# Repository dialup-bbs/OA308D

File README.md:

# OA308D
All Discrete LM308 Op-Amp - The rare, classic and out of print LM308 Op-Amp using all discrete components.

Based on detailed schematic as presented in the Linear Technology datasheet. Transistor component reference numbers are the same.

This is an untested work in progress. Please do not build if you do not know what you are doing. Three prototype boards are currently under fabrication. Any corrections, feedback, comments or recommendations are highly encouraged.

This is also my second KiCad project and as a builder, I am completely unexperienced as a circuit drafter/designer.

This project is totally influenced by MostlyDIYrf/K7TFC's OA741D.

https://github.com/mostlydiyrf/OA741D

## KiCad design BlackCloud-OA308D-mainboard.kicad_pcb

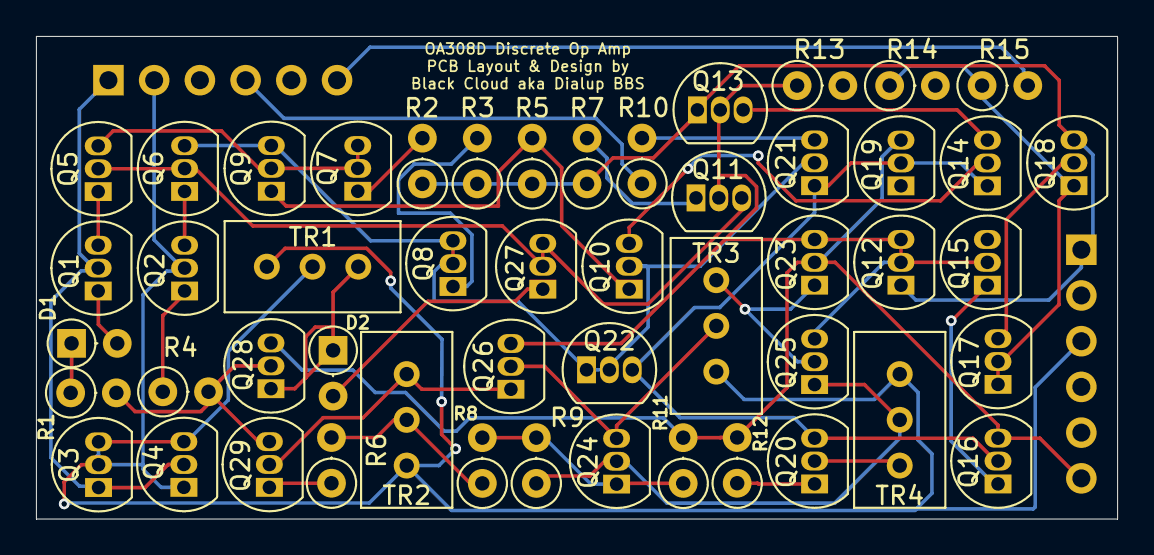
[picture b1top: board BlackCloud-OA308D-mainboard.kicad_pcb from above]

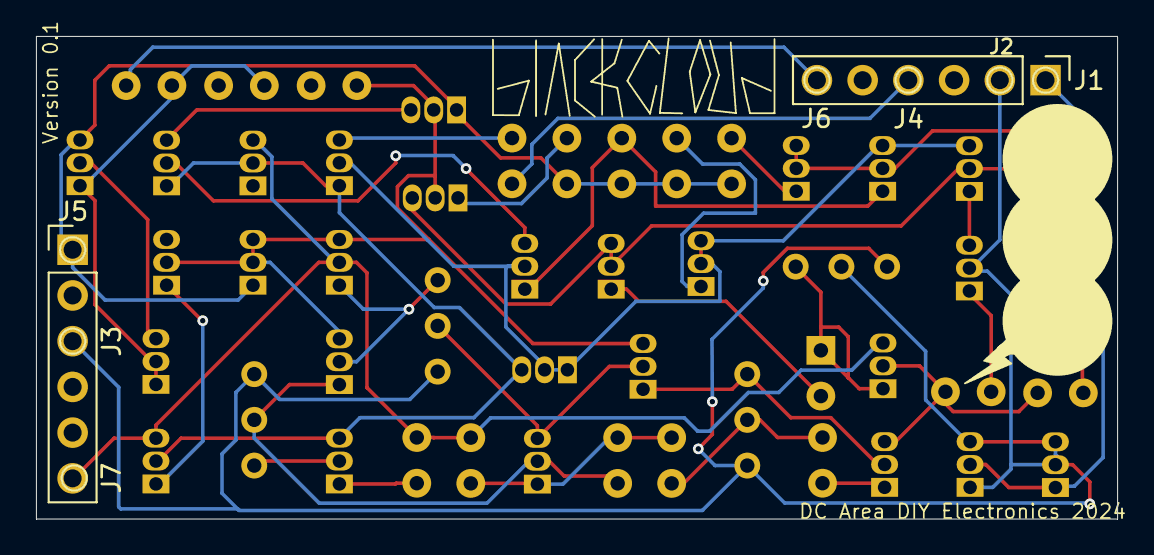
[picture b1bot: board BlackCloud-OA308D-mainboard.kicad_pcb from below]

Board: 2 copper layers, 60.1 x 26.8 mm, 57 parts (7 on the bottom side), 40 nets.

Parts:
D1, D2: 1N5711; D_DO-35_SOD27_P2.54mm_Vertical_AnodeUp
J1, J2, J5, J6, J7: Conn_01x01; TestPoint_Pad_D1.0mm
J3: Compensation 1; TestPoint_Pad_D1.0mm
J4: Compensation 8; TestPoint_Pad_D1.0mm
Q1, Q2, Q3, Q4, Q5, Q6, Q14, Q15, Q17, Q18, Q20, Q21, Q24, Q25, Q26, Q27, Q29: 2N3904; TO-92_Inline
Q7, Q8, Q9, Q10, Q11, Q12, Q16, Q19, Q28: 2N3906; TO-92_Inline
Q13: NPN; TO-92_Inline
Q22: TO-92_Inline
Q23: NJFET; TO-92_Inline
R1, R4, R13: 2k; R_Axial_DIN0207_L6.3mm_D2.5mm_P2.54mm_Vertical
R2, R3, R9: 20k; R_Axial_DIN0207_L6.3mm_D2.5mm_P2.54mm_Vertical
R5, R7: 10k; R_Axial_DIN0207_L6.3mm_D2.5mm_P2.54mm_Vertical
R6: 6.4k; R_Axial_DIN0207_L6.3mm_D2.5mm_P2.54mm_Vertical
R8: 500ohm; R_Axial_DIN0207_L6.3mm_D2.5mm_P2.54mm_Vertical
R10: 5.6k; R_Axial_DIN0207_L6.3mm_D2.5mm_P2.54mm_Vertical
R11: 1k; R_Axial_DIN0207_L6.3mm_D2.5mm_P2.54mm_Vertical
R12: 820ohm; R_Axial_DIN0207_L6.3mm_D2.5mm_P2.54mm_Vertical
R14: 240ohm; R_Axial_DIN0207_L6.3mm_D2.5mm_P2.54mm_Vertical
R15: 90ohm; R_Axial_DIN0207_L6.3mm_D2.5mm_P2.54mm_Vertical
TR1: 50k; Potentiometer_Bourns_3386C_Horizontal
TR2: 60k; Potentiometer_Bourns_3386C_Horizontal
TR3: 940ohm; Potentiometer_Bourns_3386C_Horizontal
TR4: 20k; Potentiometer_Bourns_3386C_Horizontal

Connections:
unnamed: D1.2 (A), Q1.1 (E)
unnamed: D1.1 (K), R1.1
unnamed: D2.2 (A), Q27.1 (E)
unnamed: D2.1 (K), Q28.1 (E), TR1.1
unnamed: J1.1, Q1.2 (B), Q3.1 (E), Q4.2 (B)
unnamed: J2.1, Q2.2 (B), Q4.1 (E)
unnamed: Q6.3 (C), Q8.2 (B), Q8.3 (C), Q9.3 (C), Q10.2 (B), Q21.2 (B), Q22.1 (C), Q22.2 (B)
unnamed: J4.1, R10.1
unnamed: J5.1, Q12.1 (E), Q13.1 (C), Q18.3 (C), R2.1, R3.1, R5.1, R7.1
unnamed: J6.1, R15.2
unnamed: J7.1, Q16.3 (C), Q19.3 (C), Q23.2 (G), Q28.3 (C), R11.2, R12.2
unnamed: Q1.3 (C), Q5.1 (E)
unnamed: Q2.3 (C), Q6.1 (E)
unnamed: Q2.1 (E), R4.1
unnamed: Q4.3 (C), TR1.2
unnamed: Q5.3 (C), Q7.2 (B), Q7.3 (C), Q9.2 (B)
unnamed: Q7.1 (E), R2.2
unnamed: Q8.1 (E), R3.2
unnamed: Q10.3 (C), Q14.2 (B)
unnamed: Q9.1 (E), Q10.1 (E), R5.2
unnamed: Q11.2 (B), Q12.2 (B), Q12.3 (C), Q13.2 (B), Q15.2 (B), Q23.3 (S), Q25.3 (C), Q26.3 (C), R13.1
unnamed: Q5.2 (B), Q6.2 (B), Q11.3 (C), Q27.2 (B), Q27.3 (C)
unnamed: Q11.1 (E), R7.2
unnamed: Q13.3 (E), Q14.3 (C)
unnamed: Q14.1 (E), Q16.2 (B), Q19.2 (B), Q20.3 (C), Q21.1 (E), Q22.3 (E)
unnamed: Q15.3 (C), Q17.3 (C), Q18.2 (B), R13.2
unnamed: Q15.1 (E), Q16.1 (E)
unnamed: Q17.1 (E), Q17.2 (B), Q18.1 (E), R14.1, R15.1
unnamed: Q19.1 (E), R14.2
unnamed: Q20.2 (B), TR4.1
unnamed: Q20.1 (E), R12.1
unnamed: Q21.3 (C), R10.2
unnamed: Q23.1 (D), Q25.2 (B), TR3.1
unnamed: Q24.2 (B), Q25.1 (E), R9.1, TR4.2
unnamed: Q24.3 (C), Q26.2 (B), TR3.2
unnamed: Q24.1 (E), R8.2, R9.2, R11.1
unnamed: Q26.1 (E), Q29.2 (B), TR2.1
unnamed: Q28.2 (B), Q29.3 (C), R1.2, R4.2
unnamed: Q29.1 (E), R6.1
unnamed: R6.2, R8.1, TR2.2

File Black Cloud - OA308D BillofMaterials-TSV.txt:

Reference	Value	Datasheet	Footprint	Qty	DNP
D1,D2	1N5711	https://www.microsemi.com/document-portal/doc_download/8865-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	Diode_THT:D_DO-35_SOD27_P7.62mm_Horizontal	2	
J1,J2,J5,J6,J7	Conn_01x01	~	Connector_PinHeader_2.54mm:PinHeader_1x01_P2.54mm_Vertical	5	
J3	Compensation 1	~	Connector_PinHeader_2.54mm:PinHeader_1x01_P2.54mm_Vertical	1	
J4	Compensation 8	~	Connector_PinHeader_2.54mm:PinHeader_1x01_P2.54mm_Vertical	1	
Q1,Q2,Q3,Q4,Q5,Q6,Q14,Q15,Q17,Q18,Q20,Q21,Q24,Q25,Q26,Q27,Q29	2N3904	https://www.onsemi.com/pub/Collateral/2N3903-D.PDF	Package_TO_SOT_THT:TO-92_Inline	17	
Q7,Q8,Q9,Q10,Q11,Q12,Q16,Q19,Q28	2N3906	https://www.onsemi.com/pub/Collateral/2N3906-D.PDF	Package_TO_SOT_THT:TO-92_Inline	9	
Q13	NPN	https://ngspice.sourceforge.io/docs/ngspice-html-manual/manu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	Package_TO_SOT_THT:TO-92_Inline	1	
Q22	~	https://ngspice.sourceforge.io/docs/ngspice-html-manual/manu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	Package_TO_SOT_THT:TO-92_Inline	1	
Q23	NJFET	https://ngspice.sourceforge.io/docs/ngspice-html-manual/manu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	Package_TO_SOT_THT:TO-92_Inline	1	
R1,R4,R13	2k	~	Resistor_THT:R_Axial_DIN0207_L6.3mm_D2.5mm_P2.54mm_Vertical	3	
R2,R3,R9,TR4	20k	~	-- mixed values --	4	
R5,R7	10k	~	Resistor_THT:R_Axial_DIN0207_L6.3mm_D2.5mm_P2.54mm_Vertical	2	
R6	6.4k	~	Resistor_THT:R_Axial_DIN0207_L6.3mm_D2.5mm_P2.54mm_Vertical	1	
R8	500ohm	~	Resistor_THT:R_Axial_DIN0207_L6.3mm_D2.5mm_P2.54mm_Vertical	1	
R10	5.6k	~	Resistor_THT:R_Axial_DIN0207_L6.3mm_D2.5mm_P2.54mm_Vertical	1	
R11	1k	~	Resistor_THT:R_Axial_DIN0207_L6.3mm_D2.5mm_P2.54mm_Vertical	1	
R12	820ohm	~	Resistor_THT:R_Axial_DIN0207_L6.3mm_D2.5mm_P2.54mm_Vertical	1	
R14	240ohm	~	Resistor_THT:R_Axial_DIN0207_L6.3mm_D2.5mm_P2.54mm_Vertical	1	
R15	90ohm	~	Resistor_THT:R_Axial_DIN0207_L6.3mm_D2.5mm_P2.54mm_Vertical	1	
TR1	50k	~	Potentiometer_THT:Potentiometer_Bourns_3386C_Horizontal	1	
TR2	60k	~	Potentiometer_THT:Potentiometer_Bourns_3386C_Horizontal	1	
TR3	940ohm	~	Potentiometer_THT:Potentiometer_Bourns_3386C_Horizontal	1

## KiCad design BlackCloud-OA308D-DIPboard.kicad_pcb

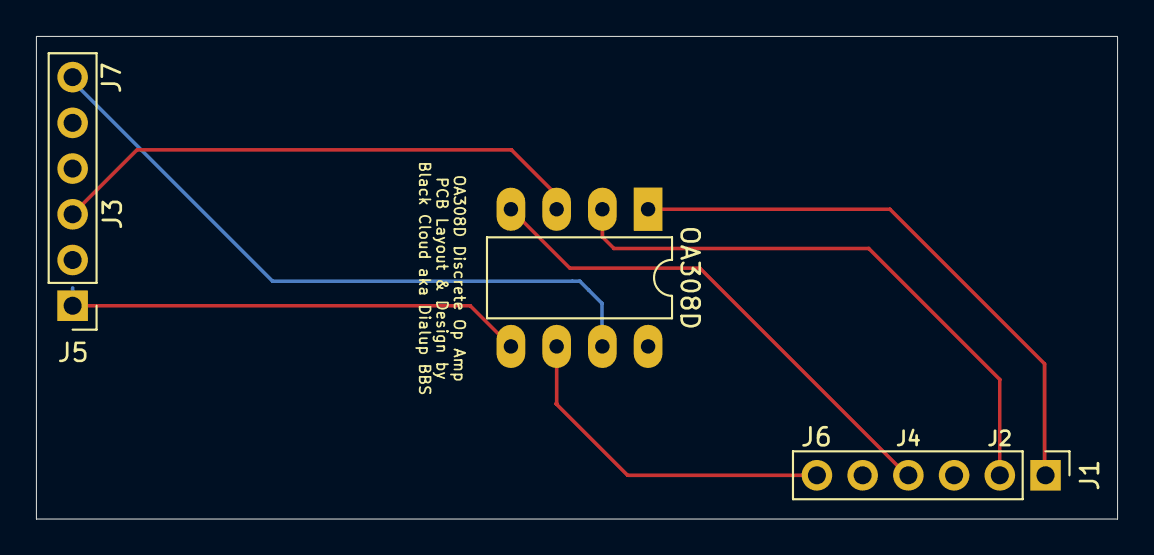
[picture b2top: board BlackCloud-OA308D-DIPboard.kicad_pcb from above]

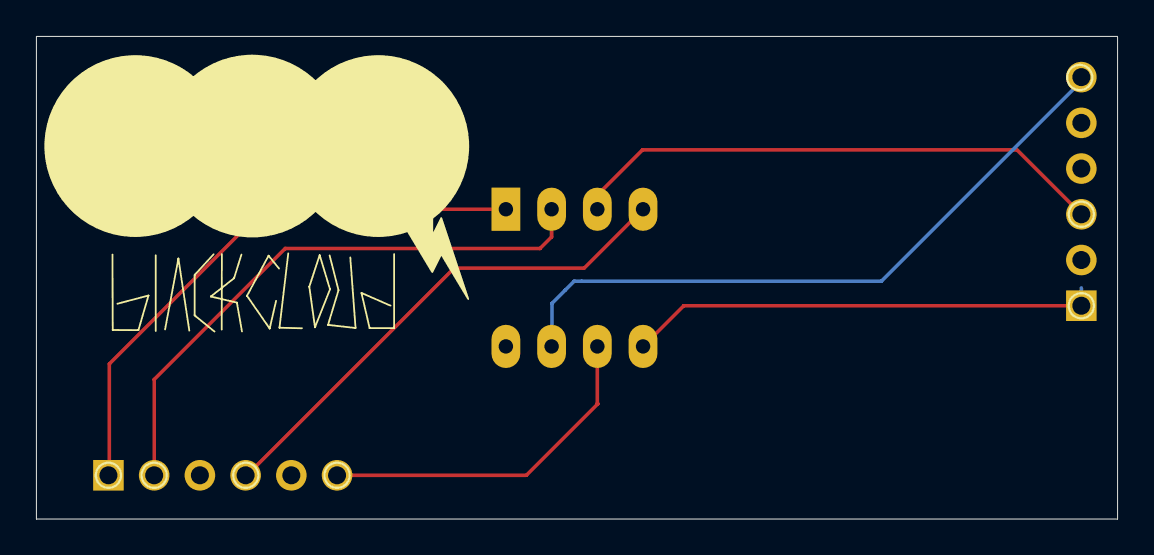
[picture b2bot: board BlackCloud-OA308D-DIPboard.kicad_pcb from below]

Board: 2 copper layers, 60.1 x 26.8 mm, 8 parts (7 on the bottom side), 6 nets.

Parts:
J1, J2, J5, J6, J7: Conn_01x01; TestPoint_Pad_D1.0mm
J3: Compensation 1; TestPoint_Pad_D1.0mm
J4: Compensation 8; TestPoint_Pad_D1.0mm
OA308D: DIP-8_W7.62mm_LongPads

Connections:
unnamed: J1.1, OA308D.1
unnamed: J2.1, OA308D.2
unnamed: J4.1, OA308D.4
unnamed: J5.1, OA308D.5
unnamed: J6.1, OA308D.6
unnamed: J7.1, OA308D.7
